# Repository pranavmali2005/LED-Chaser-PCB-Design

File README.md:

# 555 Timer and CD4017 LED Chaser PCB Design

## Project Overview
A circular LED Chaser circuit designed using KiCad 10, based on the NE555 timer and CD4017 decade counter ICs.

The project includes circuit schematic design, PCB layout, routing and Gerber generation.

### 1. 555 Timer + CD4017 LED Chaser PCB Design
- Designed a circular PCB using KiCad 10.
- Completed schematic capture, PCB layout and routing.
- Generated Gerber and Excellon drill files.
- Created a 3D PCB visualization.

[View Project](https://github.com/pranavmali2005/LED-Chaser-PCB-Design)

## Tools Used
- KiCad 10
- NE555 Timer IC
- CD4017 Decade Counter

## Project Features
- Circular PCB layout
- Multiple LED outputs
- Schematic capture
- PCB component placement and routing
- Gerber and Excellon drill file generation

## Project Files
| Folder | Contents |
|---|---|
| KiCad_Project | Original KiCad source files |
| Schematic | Schematic PDF |
| PCB_Layout | PCB layout and 3D view images |
| Gerber_Files | Manufacturing Gerber and drill files |

## PCB Design Preview

### PCB Layout

### 3D PCB View

## Schematic
[View Schematic PDF](Schematic/LED_chaser_ckt.pdf)

## Manufacturing Files
[Download Gerber Files](Gerber_Files/)

## Design Status
- Schematic: Completed
- PCB layout: Completed
- Gerber generation: Completed
- Physical fabrication and testing: Not performed

## Author
Pranav Mali

B.Tech Electronics and Computer Science Engineering  
PVPIT, Sangli | 2027 Batch

[GitHub Profile](https://github.com/pranavmali2005)

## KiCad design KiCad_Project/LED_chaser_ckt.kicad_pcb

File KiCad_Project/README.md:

# KiCad Source Project

This folder contains the original KiCad 10 project files.

- .kicad_pro – Project configuration
- .kicad_sch – Circuit schematic
- .kicad_pcb – PCB layout

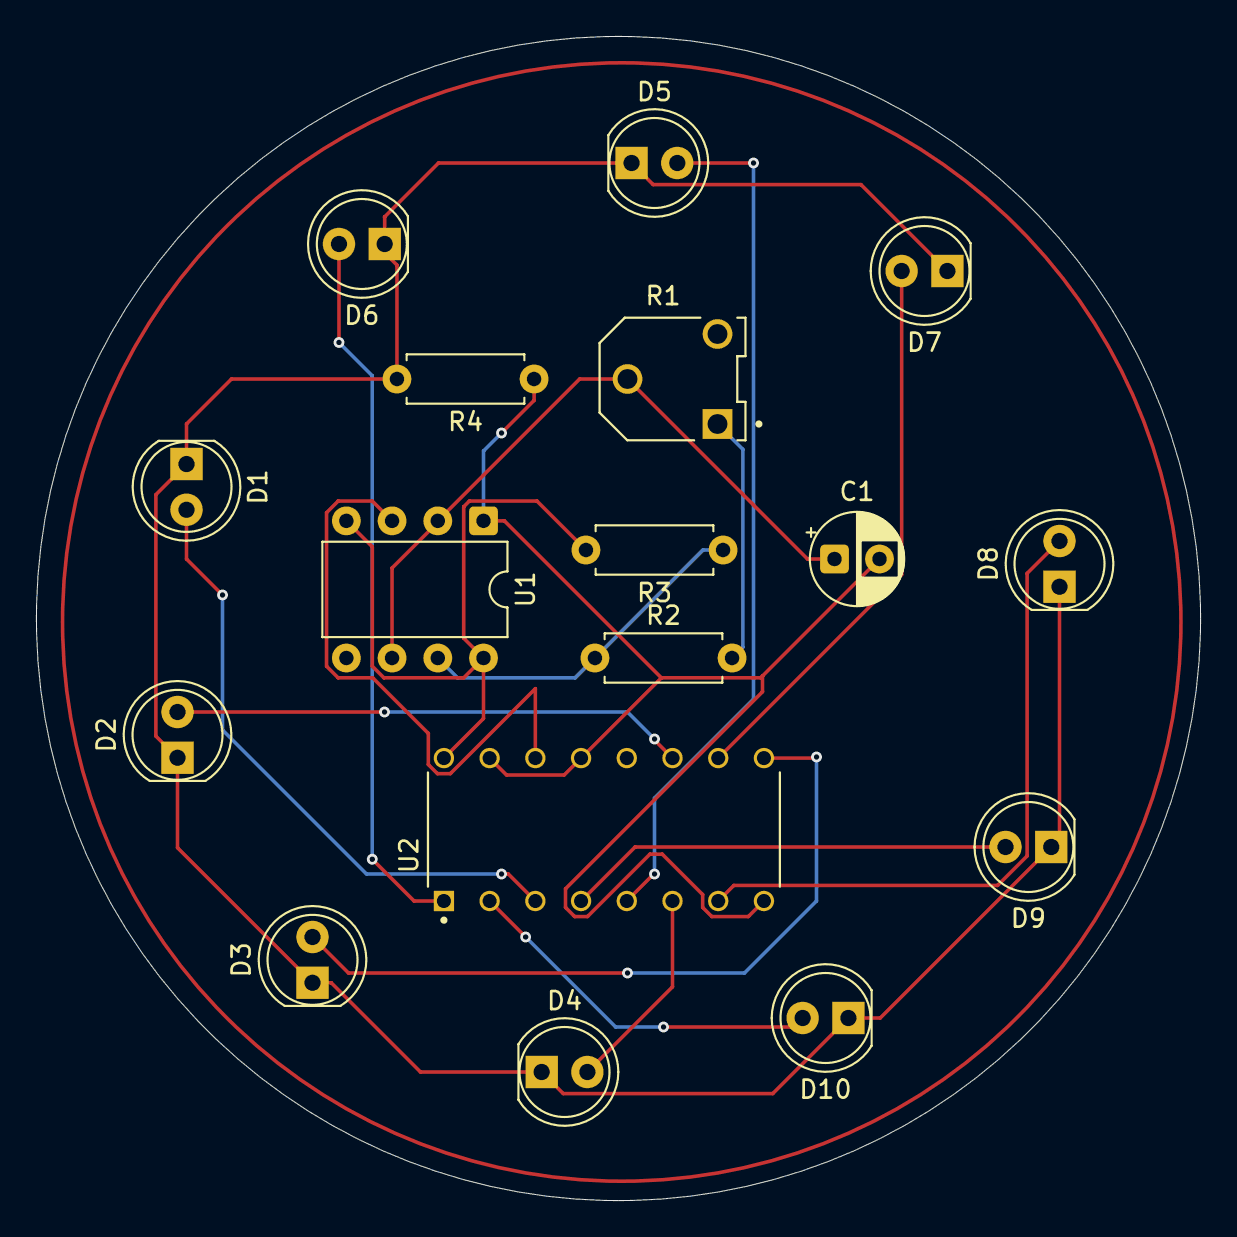
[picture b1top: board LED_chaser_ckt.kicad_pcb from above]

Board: 2 copper layers, 64.7 x 64.7 mm, 17 parts (0 on the bottom side), 17 nets.

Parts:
C1: C_Polarized; CP_Radial_D5.0mm_P2.50mm
D1, D2, D3, D4, D5, D6, D7, D8, D9, D10: LED; LED_D5.0mm
R1: 3306F-1-103; TRIM_3306F-1-103
R2, R3, R4: R; R_Axial_DIN0207_L6.3mm_D2.5mm_P7.62mm_Horizontal
U1: NE555P; DIP-8_W7.62mm
U2: CD4017BE; DIP794W45P254L1969H508Q16

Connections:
unnamed: D1.2 (A), U2.3 (O)
unnamed: D1.1 (K), D2.1 (K), D3.1 (K), D4.1 (K), D5.1 (K), D6.1 (K), D7.1 (K), D8.1 (K), D9.1 (K), D10.1 (K), R4.2
unnamed: D2.2 (A), U2.11 (9)
unnamed: D3.2 (A), U2.9 (8)
unnamed: D4.2 (A), U2.6 (7)
unnamed: D5.2 (A), U2.5 (6)
unnamed: D6.2 (A), U2.1 (5)
unnamed: D7.2 (A), U2.10 (4)
unnamed: D8.2 (A), U2.7 (3)
unnamed: D9.2 (A), U2.4 (2)
unnamed: D10.2 (A), U2.2 (1)
unnamed: R1.1, R2.2
unnamed: R2.1, R3.1, U1.7 (DISCH)
unnamed: C1.2, R4.1, U1.1 (GND), U2.8 (VSS), U2.13 (CLOCK_INHIBIT), U2.15 (RESET)
unnamed: U1.3 (OUT), U2.14 (CLOCK)
unnamed: C1.1, R1.2, U1.2 (TRIG), U1.6 (THRES)
unnamed: R3.2, U1.4 (~RST), U1.8 (VCC), U2.16 (VDD)
